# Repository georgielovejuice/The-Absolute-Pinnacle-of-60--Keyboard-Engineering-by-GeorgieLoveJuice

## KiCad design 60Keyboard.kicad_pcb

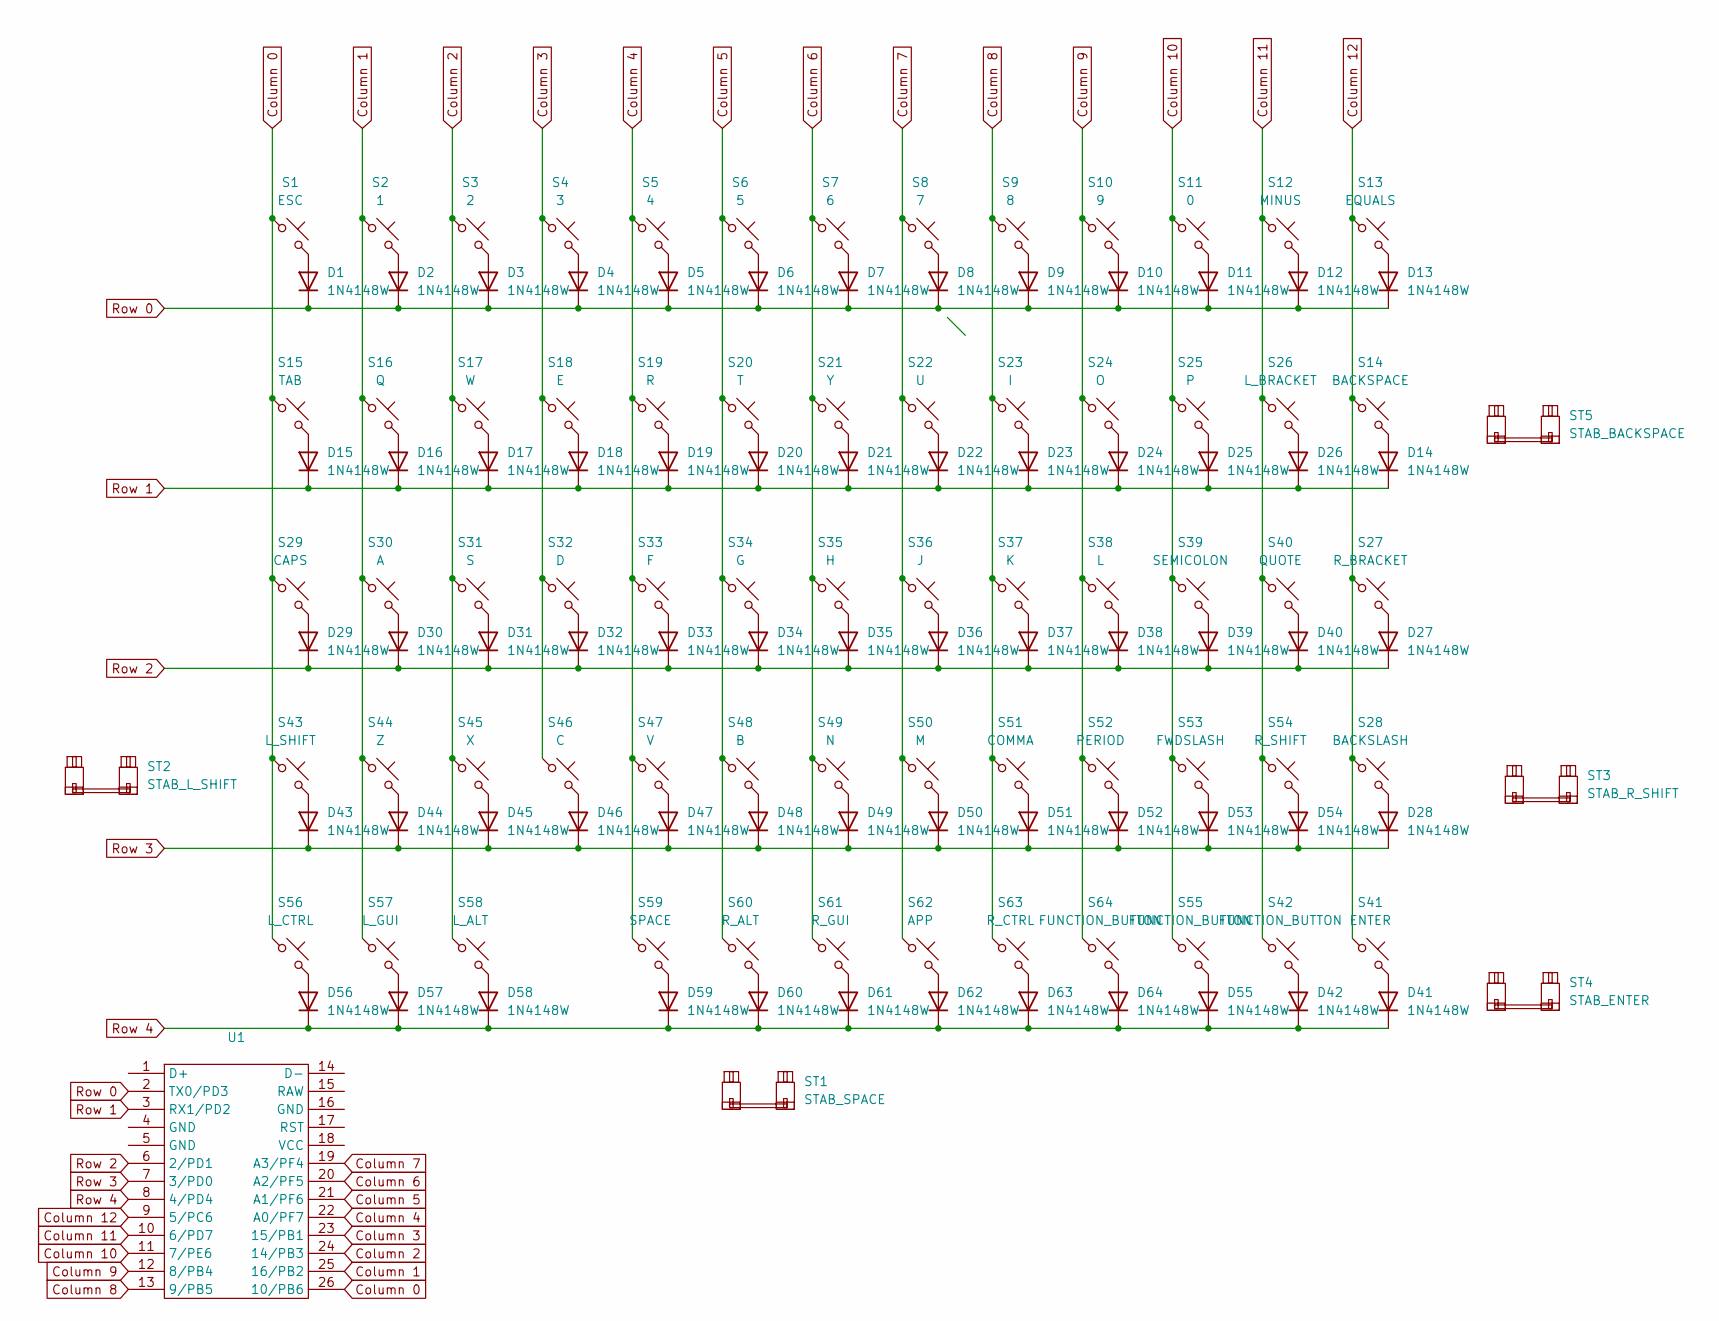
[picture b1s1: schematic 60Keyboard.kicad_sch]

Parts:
D1, D2, D3, D4, D5, D6, D7, D8, D9, D10, D11, D12, D13, D14, D15, D16, D17, D18, D19, D20, D21, D22, D23, D24, D25, D26, D27, D28, D29, D30, D31, D32, D33, D34, D35, D36, D37, D38, D39, D40, D41, D42, D43, D44, D45, D46, D47, D48, D49, D50, D51, D52, D53, D54, D55, D56, D57, D58, D59, D60, D61, D62, D63, D64: 1N4148W; D_SOD-123
S1: ESC; MX_PCB_1.00u
S2: 1; MX_PCB_1.00u
S3: 2; MX_PCB_1.00u
S4: 3; MX_PCB_1.00u
S5: 4; MX_PCB_1.00u
S6: 5; MX_PCB_1.00u
S7: 6; MX_PCB_1.00u
S8: 7; MX_PCB_1.00u
S9: 8; MX_PCB_1.00u
S10: 9; MX_PCB_1.00u
S11: 0; MX_PCB_1.00u
S12: MINUS; MX_PCB_1.00u
S13: EQUALS; MX_PCB_1.00u
S14: BACKSPACE; MX_PCB_2.00u
S15: TAB; MX_PCB_1.50u
S16: Q; MX_PCB_1.00u
S17: W; MX_PCB_1.00u
S18: E; MX_PCB_1.00u
S19: R; MX_PCB_1.00u
S20: T; MX_PCB_1.00u
S21: Y; MX_PCB_1.00u
S22: U; MX_PCB_1.00u
S23: I; MX_PCB_1.00u
S24: O; MX_PCB_1.00u
S25: P; MX_PCB_1.00u
S26: L_BRACKET; MX_PCB_1.00u
S27: R_BRACKET; MX_PCB_1.00u
S28: BACKSLASH; MX_PCB_1.50u
S29: CAPS; MX_PCB_1.75u
S30: A; MX_PCB_1.00u
S31: S; MX_PCB_1.00u
S32: D; MX_PCB_1.00u
S33: F; MX_PCB_1.00u
S34: G; MX_PCB_1.00u
S35: H; MX_PCB_1.00u
S36: J; MX_PCB_1.00u
S37: K; MX_PCB_1.00u
S38: L; MX_PCB_1.00u
S39: SEMICOLON; MX_PCB_1.00u
S40: QUOTE; MX_PCB_1.00u
S41: ENTER; MX_PCB_2.25u
S42, S55, S64: FUNCTION_BUTTON; MX_PCB_1.00u
S43: L_SHIFT; MX_PCB_2.25u
S44: Z; MX_PCB_1.00u
S45: X; MX_PCB_1.00u
S46: C; MX_PCB_1.00u
S47: V; MX_PCB_1.00u
S48: B; MX_PCB_1.00u
S49: N; MX_PCB_1.00u
S50: M; MX_PCB_1.00u
S51: COMMA; MX_PCB_1.00u
S52: PERIOD; MX_PCB_1.00u
S53: FWDSLASH; MX_PCB_1.00u
S54: R_SHIFT; MX_PCB_2.75u
S56: L_CTRL; MX_PCB_1.25u
S57: L_GUI; MX_PCB_1.25u
S58: L_ALT; MX_PCB_1.25u
S59: SPACE; MX_PCB_6.25u
S60: R_ALT; MX_PCB_1.25u
S61: R_GUI; MX_PCB_1.25u
S62: APP; MX_PCB_1.25u
S63: R_CTRL; MX_PCB_1.25u
ST1: STAB_SPACE; STAB_MX_P_6.25u
ST2: STAB_L_SHIFT; STAB_MX_P_2.25u
ST3: STAB_R_SHIFT; STAB_MX_P_2.75u
ST4: STAB_ENTER; STAB_MX_P_2.25u
ST5: STAB_BACKSPACE; STAB_MX_P_2u
U1: Adafruit_KB2040

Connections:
Column 0: S1.1, S15.1, S29.1, S43.1, S56.1, U1.26 (10/PB6)
Column 1: S2.1, S16.1, S30.1, S44.1, S57.1, U1.25 (16/PB2)
Column 2: S3.1, S17.1, S31.1, S45.1, S58.1, U1.24 (14/PB3)
Column 3: S4.1, S18.1, S32.1, S46.1, U1.23 (15/PB1)
Column 4: S5.1, S19.1, S33.1, S47.1, S59.1, U1.22 (A0/PF7)
Column 5: S6.1, S20.1, S34.1, S48.1, S60.1, U1.21 (A1/PF6)
Column 6: S7.1, S21.1, S35.1, S49.1, S61.1, U1.20 (A2/PF5)
Column 7: S8.1, S22.1, S36.1, S50.1, S62.1, U1.19 (A3/PF4)
Column 8: S9.1, S23.1, S37.1, S51.1, S63.1, U1.13 (9/PB5)
Column 9: S10.1, S24.1, S38.1, S52.1, S64.1, U1.12 (8/PB4)
Column 10: S11.1, S25.1, S39.1, S53.1, S55.1, U1.11 (7/PE6)
Column 11: S12.1, S26.1, S40.1, S42.1, S54.1, U1.10 (6/PD7)
Column 12: S13.1, S14.1, S27.1, S28.1, S41.1, U1.9 (5/PC6)
unnamed: D1.2 (A), S1.2
unnamed: D2.2 (A), S2.2
unnamed: D3.2 (A), S3.2
unnamed: D4.2 (A), S4.2
unnamed: D5.2 (A), S5.2
unnamed: D6.2 (A), S6.2
unnamed: D7.2 (A), S7.2
unnamed: D8.2 (A), S8.2
unnamed: D9.2 (A), S9.2
unnamed: D10.2 (A), S10.2
unnamed: D11.2 (A), S11.2
unnamed: D12.2 (A), S12.2
unnamed: D13.2 (A), S13.2
unnamed: D14.2 (A), S14.2
unnamed: D15.2 (A), S15.2
unnamed: D16.2 (A), S16.2
unnamed: D17.2 (A), S17.2
unnamed: D18.2 (A), S18.2
unnamed: D19.2 (A), S19.2
unnamed: D20.2 (A), S20.2
unnamed: D21.2 (A), S21.2
unnamed: D22.2 (A), S22.2
unnamed: D23.2 (A), S23.2
unnamed: D24.2 (A), S24.2
unnamed: D25.2 (A), S25.2
unnamed: D26.2 (A), S26.2
unnamed: D27.2 (A), S27.2
unnamed: D28.2 (A), S28.2
unnamed: D29.2 (A), S29.2
unnamed: D30.2 (A), S30.2
unnamed: D31.2 (A), S31.2
unnamed: D32.2 (A), S32.2
unnamed: D33.2 (A), S33.2
unnamed: D34.2 (A), S34.2
unnamed: D35.2 (A), S35.2
unnamed: D36.2 (A), S36.2
unnamed: D37.2 (A), S37.2
unnamed: D38.2 (A), S38.2
unnamed: D39.2 (A), S39.2
unnamed: D40.2 (A), S40.2
unnamed: D41.2 (A), S41.2
unnamed: D42.2 (A), S42.2
unnamed: D43.2 (A), S43.2
unnamed: D44.2 (A), S44.2
unnamed: D45.2 (A), S45.2
unnamed: D46.2 (A), S46.2
unnamed: D47.2 (A), S47.2
unnamed: D48.2 (A), S48.2
unnamed: D49.2 (A), S49.2
unnamed: D50.2 (A), S50.2
unnamed: D51.2 (A), S51.2
unnamed: D52.2 (A), S52.2
unnamed: D53.2 (A), S53.2
unnamed: D54.2 (A), S54.2
unnamed: D55.2 (A), S55.2
unnamed: D56.2 (A), S56.2
unnamed: D57.2 (A), S57.2
unnamed: D58.2 (A), S58.2
unnamed: D59.2 (A), S59.2
unnamed: D60.2 (A), S60.2
unnamed: D61.2 (A), S61.2
unnamed: D62.2 (A), S62.2
unnamed: D63.2 (A), S63.2
unnamed: D64.2 (A), S64.2
Row 0: D1.1 (K), D2.1 (K), D3.1 (K), D4.1 (K), D5.1 (K), D6.1 (K), D7.1 (K), D8.1 (K), D9.1 (K), D10.1 (K), D11.1 (K), D12.1 (K), D13.1 (K), U1.2 (TX0/PD3)
Row 1: D14.1 (K), D15.1 (K), D16.1 (K), D17.1 (K), D18.1 (K), D19.1 (K), D20.1 (K), D21.1 (K), D22.1 (K), D23.1 (K), D24.1 (K), D25.1 (K), D26.1 (K), U1.3 (RX1/PD2)
Row 2: D27.1 (K), D29.1 (K), D30.1 (K), D31.1 (K), D32.1 (K), D33.1 (K), D34.1 (K), D35.1 (K), D36.1 (K), D37.1 (K), D38.1 (K), D39.1 (K), D40.1 (K), U1.6 (2/PD1)
Row 3: D28.1 (K), D43.1 (K), D44.1 (K), D45.1 (K), D46.1 (K), D47.1 (K), D48.1 (K), D49.1 (K), D50.1 (K), D51.1 (K), D52.1 (K), D53.1 (K), D54.1 (K), U1.7 (3/PD0)
Row 4: D41.1 (K), D42.1 (K), D55.1 (K), D56.1 (K), D57.1 (K), D58.1 (K), D59.1 (K), D60.1 (K), D61.1 (K), D62.1 (K), D63.1 (K), D64.1 (K), U1.8 (4/PD4)

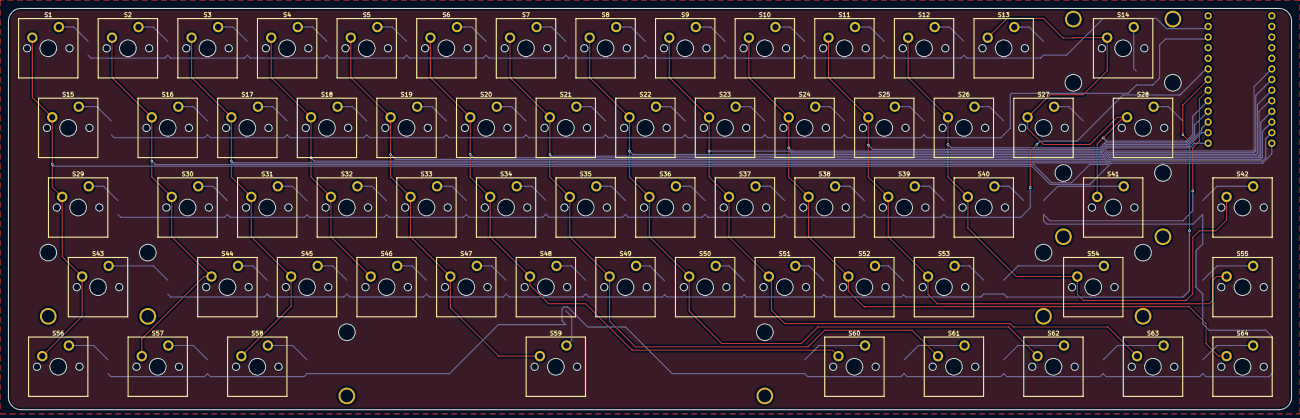
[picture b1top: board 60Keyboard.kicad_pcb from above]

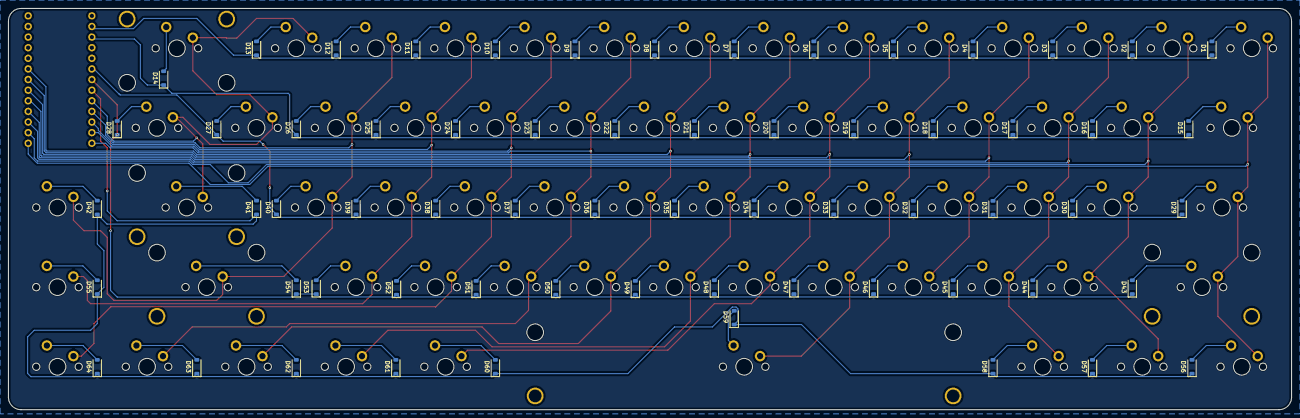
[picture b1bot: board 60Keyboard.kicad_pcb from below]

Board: 2 copper layers, 307.0 x 96.0 mm, 134 parts (64 on the bottom side), 82 nets.

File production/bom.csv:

Designator,Footprint,Quantity,Value,LCSC Part #
"D1, D10, D11, D12, D13, D14, D15, D16, D17, D18, D19, D2, D20, D21, D22, D23, D24, D25, D26, D27, D28, D29, D3, D30, D31, D32, D33, D34, D35, D36, D37, D38, D39, D4, D40, D41, D42, D43, D44, D45, D46, D47, D48, D49, D5, D50, D51, D52, D53, D54, D55, D56, D57, D58, D59, D6, D60, D61, D62, D63, D64, D7, D8, D9",D_SOD-123,64,1N4148W,
S1,MX_PCB_1.00u,1,ESC,
S10,MX_PCB_1.00u,1,9,
S11,MX_PCB_1.00u,1,0,
S12,MX_PCB_1.00u,1,MINUS,
S13,MX_PCB_1.00u,1,EQUALS,
S14,MX_PCB_2.00u,1,BACKSPACE,
S15,MX_PCB_1.50u,1,TAB,
S16,MX_PCB_1.00u,1,Q,
S17,MX_PCB_1.00u,1,W,
S18,MX_PCB_1.00u,1,E,
S19,MX_PCB_1.00u,1,R,
S2,MX_PCB_1.00u,1,1,
S20,MX_PCB_1.00u,1,T,
S21,MX_PCB_1.00u,1,Y,
S22,MX_PCB_1.00u,1,U,
S23,MX_PCB_1.00u,1,I,
S24,MX_PCB_1.00u,1,O,
S25,MX_PCB_1.00u,1,P,
S26,MX_PCB_1.00u,1,L_BRACKET,
S27,MX_PCB_1.00u,1,R_BRACKET,
S28,MX_PCB_1.50u,1,BACKSLASH,
S29,MX_PCB_1.75u,1,CAPS,
S3,MX_PCB_1.00u,1,2,
S30,MX_PCB_1.00u,1,A,
S31,MX_PCB_1.00u,1,S,
S32,MX_PCB_1.00u,1,D,
S33,MX_PCB_1.00u,1,F,
S34,MX_PCB_1.00u,1,G,
S35,MX_PCB_1.00u,1,H,
S36,MX_PCB_1.00u,1,J,
S37,MX_PCB_1.00u,1,K,
S38,MX_PCB_1.00u,1,L,
S39,MX_PCB_1.00u,1,SEMICOLON,
S4,MX_PCB_1.00u,1,3,
S40,MX_PCB_1.00u,1,QUOTE,
S41,MX_PCB_2.25u,1,ENTER,
"S42, S55, S64",MX_PCB_1.00u,3,FUNCTION_BUTTON,
S43,MX_PCB_2.25u,1,L_SHIFT,
S44,MX_PCB_1.00u,1,Z,
S45,MX_PCB_1.00u,1,X,
S46,MX_PCB_1.00u,1,C,
S47,MX_PCB_1.00u,1,V,
S48,MX_PCB_1.00u,1,B,
S49,MX_PCB_1.00u,1,N,
S5,MX_PCB_1.00u,1,4,
S50,MX_PCB_1.00u,1,M,
S51,MX_PCB_1.00u,1,COMMA,
S52,MX_PCB_1.00u,1,PERIOD,
S53,MX_PCB_1.00u,1,FWDSLASH,
S54,MX_PCB_2.75u,1,R_SHIFT,
S56,MX_PCB_1.25u,1,L_CTRL,
S57,MX_PCB_1.25u,1,L_GUI,
S58,MX_PCB_1.25u,1,L_ALT,
S59,MX_PCB_6.25u,1,SPACE,
S6,MX_PCB_1.00u,1,5,
S60,MX_PCB_1.25u,1,R_ALT,
S61,MX_PCB_1.25u,1,R_GUI,
S62,MX_PCB_1.25u,1,APP,
S63,MX_PCB_1.25u,1,R_CTRL,
S7,MX_PCB_1.00u,1,6,
S8,MX_PCB_1.00u,1,7,
S9,MX_PCB_1.00u,1,8,
ST1,STAB_MX_P_6.25u,1,STAB_SPACE,
ST2,STAB_MX_P_2.25u,1,STAB_L_SHIFT,
ST3,STAB_MX_P_2.75u,1,STAB_R_SHIFT,
ST4,STAB_MX_P_2.25u,1,STAB_ENTER,
ST5,STAB_MX_P_2u,1,STAB_BACKSPACE,
U1,Adafruit_KB2040,1,~,

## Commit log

2025-03-21 updated edge cut & manufacturing files
2025-04-03 modify measurement & Case and Plate
2025-04-03 add library
2025-04-08 updated plate
2025-04-11 finalisation
